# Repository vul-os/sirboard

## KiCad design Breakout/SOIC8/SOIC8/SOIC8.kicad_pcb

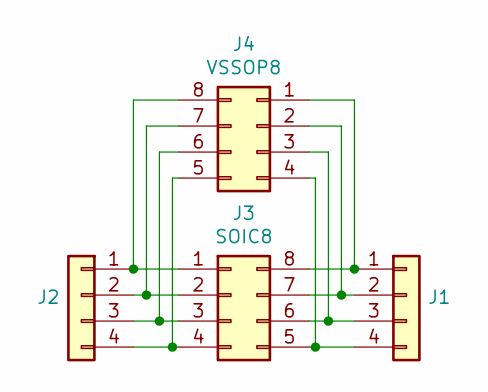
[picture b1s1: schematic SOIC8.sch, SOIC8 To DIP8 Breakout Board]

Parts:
J1, J2: Conn_01x04; PinHeader_1x04_P2.54mm_Vertical
J3: SOIC8; SOIC-8_3.9x4.9mm_P1.27mm
J4: VSSOP8; VSSOP-8_2.3x2mm_P0.5mm

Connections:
unnamed: J1.1, J3.8, J4.1
unnamed: J1.2, J3.7, J4.2
unnamed: J1.3, J3.6, J4.3
unnamed: J1.4, J3.5, J4.4
unnamed: J2.1, J3.1, J4.8
unnamed: J2.2, J3.2, J4.7
unnamed: J2.3, J3.3, J4.6
unnamed: J2.4, J3.4, J4.5

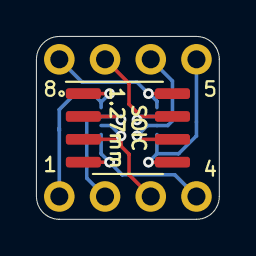
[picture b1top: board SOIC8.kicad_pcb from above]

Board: 2 copper layers, 10.2 x 10.2 mm, 4 parts (1 on the bottom side), 8 nets.

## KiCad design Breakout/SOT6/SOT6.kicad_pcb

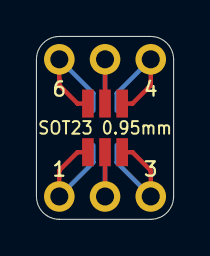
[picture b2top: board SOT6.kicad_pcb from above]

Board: 2 copper layers, 7.6 x 10.2 mm, 4 parts (1 on the bottom side), 6 nets.

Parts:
J1, J2: Conn_01x03; PinHeader_1x03_P2.54mm_Vertical
J3: Conn_02x03_Counter_Clockwise; SOT-23-6_Handsoldering
J4: Conn_02x03_Counter_Clockwise; SOT-363_SC-70-6_Handsoldering

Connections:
unnamed: J1.1, J3.6, J4.1
unnamed: J1.2, J3.5, J4.2
unnamed: J1.3, J3.4, J4.3
unnamed: J2.1, J3.1, J4.6
unnamed: J2.2, J3.2, J4.5
unnamed: J2.3, J3.3, J4.4

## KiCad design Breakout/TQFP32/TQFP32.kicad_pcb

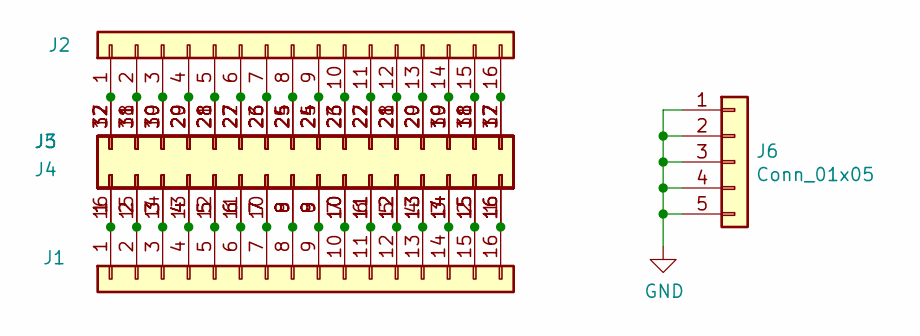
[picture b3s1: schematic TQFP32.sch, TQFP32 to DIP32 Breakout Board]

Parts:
J1, J2: Conn_01x16; PinHeader_1x16_P2.54mm_Vertical
J3: Conn_02x16_Counter_Clockwise; TQFP-32_7x7mm_P0.8mm
J4: Conn_02x16_Counter_Clockwise; LQFP-32_5x5mm_P0.5mm
J5: Conn_02x16_Counter_Clockwise; QFN-32-1EP_4x4mm_P0.4mm_EP2.65x2.65mm
J6: Conn_01x05; PinHeader_1x05_P2.54mm_Vertical

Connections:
GND: J5.33, J6.1, J6.2, J6.3, J6.4, J6.5
unnamed: J1.1, J3.1, J4.16, J5.1
unnamed: J1.2, J3.2, J4.15, J5.2
unnamed: J1.3, J3.3, J4.14, J5.3
unnamed: J1.4, J3.4, J4.13, J5.4
unnamed: J1.5, J3.5, J4.12, J5.5
unnamed: J1.6, J3.6, J4.11, J5.6
unnamed: J1.7, J3.7, J4.10, J5.7
unnamed: J1.8, J3.8, J4.9, J5.8
unnamed: J1.9, J3.9, J4.8, J5.9
unnamed: J1.10, J3.10, J4.7, J5.10
unnamed: J1.11, J3.11, J4.6, J5.11
unnamed: J1.12, J3.12, J4.5, J5.12
unnamed: J1.13, J3.13, J4.4, J5.13
unnamed: J1.14, J3.14, J4.3, J5.14
unnamed: J1.15, J3.15, J4.2, J5.15
unnamed: J1.16, J3.16, J4.1, J5.16
unnamed: J2.1, J3.32, J4.17, J5.32
unnamed: J2.2, J3.31, J4.18, J5.31
unnamed: J2.3, J3.30, J4.19, J5.30
unnamed: J2.4, J3.29, J4.20, J5.29
unnamed: J2.5, J3.28, J4.21, J5.28
unnamed: J2.6, J3.27, J4.22, J5.27
unnamed: J2.7, J3.26, J4.23, J5.26
unnamed: J2.8, J3.25, J4.24, J5.25
unnamed: J2.9, J3.24, J4.25, J5.24
unnamed: J2.10, J3.23, J4.26, J5.23
unnamed: J2.11, J3.22, J4.27, J5.22
unnamed: J2.12, J3.21, J4.28, J5.21
unnamed: J2.13, J3.20, J4.29, J5.20
unnamed: J2.14, J3.19, J4.30, J5.19
unnamed: J2.15, J3.18, J4.31, J5.18
unnamed: J2.16, J3.17, J4.32, J5.17

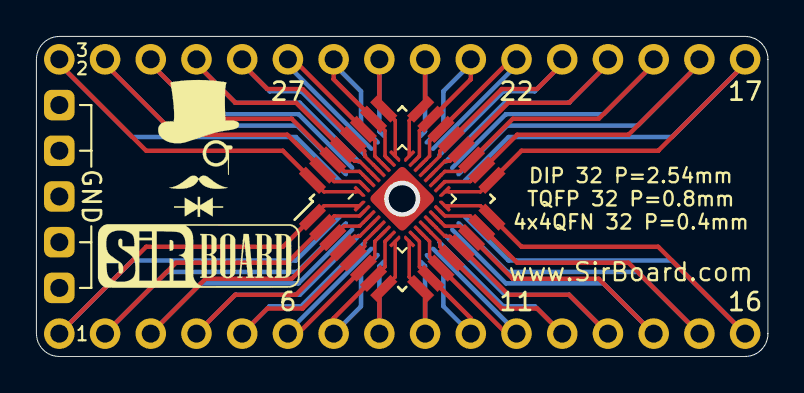
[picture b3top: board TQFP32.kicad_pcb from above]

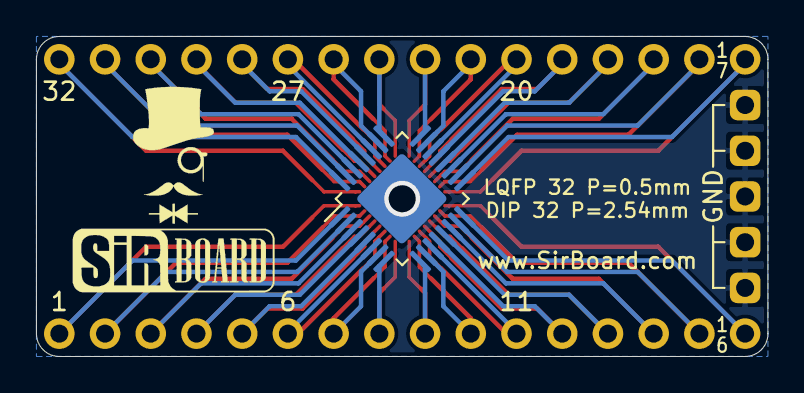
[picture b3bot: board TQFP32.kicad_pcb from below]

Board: 2 copper layers, 40.6 x 17.8 mm, 6 parts (3 on the bottom side), 33 nets.

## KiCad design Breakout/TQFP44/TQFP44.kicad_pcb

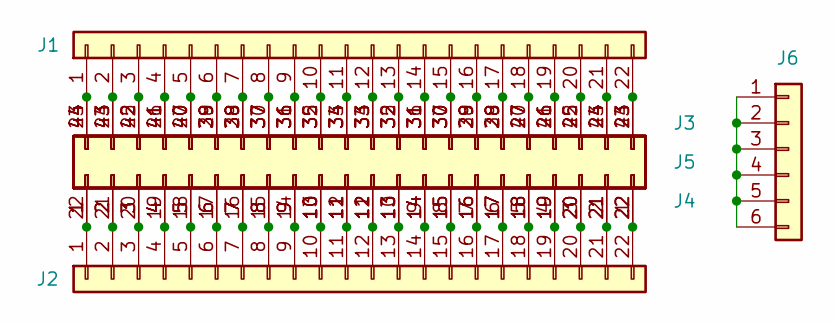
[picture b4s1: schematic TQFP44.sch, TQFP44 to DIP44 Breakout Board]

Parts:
J1, J2: Conn_01x22; PinHeader_1x22_P2.54mm_Vertical
J3, J5: Conn_02x22_Counter_Clockwise; TQFP-44_10x10mm_P0.8mm
J4: Conn_02x22_Counter_Clockwise; QFN-44-1EP_7x7mm_P0.5mm_EP5.15x5.15mm
J6: Conn_01x06; PinHeader_1x06_P2.54mm_Horizontal

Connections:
unnamed: J1.1, J3.44, J4.44, J5.23
unnamed: J1.2, J3.43, J4.43, J5.24
unnamed: J1.3, J3.42, J4.42, J5.25
unnamed: J1.4, J3.41, J4.41, J5.26
unnamed: J1.5, J3.40, J4.40, J5.27
unnamed: J1.6, J3.39, J4.39, J5.28
unnamed: J1.7, J3.38, J4.38, J5.29
unnamed: J1.8, J3.37, J4.37, J5.30
unnamed: J1.9, J3.36, J4.36, J5.31
unnamed: J1.10, J3.35, J4.35, J5.32
unnamed: J1.11, J3.34, J4.34, J5.33
unnamed: J1.12, J3.33, J4.33, J5.34
unnamed: J1.13, J3.32, J4.32, J5.35
unnamed: J1.14, J3.31, J4.31, J5.36
unnamed: J1.15, J3.30, J4.30, J5.37
unnamed: J1.16, J3.29, J4.29, J5.38
unnamed: J1.17, J3.28, J4.28, J5.39
unnamed: J1.18, J3.27, J4.27, J5.40
unnamed: J1.19, J3.26, J4.26, J5.41
unnamed: J1.20, J3.25, J4.25, J5.42
unnamed: J1.21, J3.24, J4.24, J5.43
unnamed: J1.22, J3.23, J4.23, J5.44
unnamed: J2.1, J3.1, J4.1, J5.22
unnamed: J2.2, J3.2, J4.2, J5.21
unnamed: J2.3, J3.3, J4.3, J5.20
unnamed: J2.4, J3.4, J4.4, J5.19
unnamed: J2.5, J3.5, J4.5, J5.18
unnamed: J2.6, J3.6, J4.6, J5.17
unnamed: J2.7, J3.7, J4.7, J5.16
unnamed: J2.8, J3.8, J4.8, J5.15
unnamed: J2.9, J3.9, J4.9, J5.14
unnamed: J2.10, J3.10, J4.10, J5.13
unnamed: J2.11, J3.11, J4.11, J5.12
unnamed: J2.12, J3.12, J4.12, J5.11
unnamed: J2.13, J3.13, J4.13, J5.10
unnamed: J2.14, J3.14, J4.14, J5.9
unnamed: J2.15, J3.15, J4.15, J5.8
unnamed: J2.16, J3.16, J4.16, J5.7
unnamed: J2.17, J3.17, J4.17, J5.6
unnamed: J2.18, J3.18, J4.18, J5.5
unnamed: J2.19, J3.19, J4.19, J5.4
unnamed: J2.20, J3.20, J4.20, J5.3
unnamed: J2.21, J3.21, J4.21, J5.2
unnamed: J2.22, J3.22, J4.22, J5.1
unnamed: J4.45, J6.1, J6.2, J6.3, J6.4, J6.5, J6.6

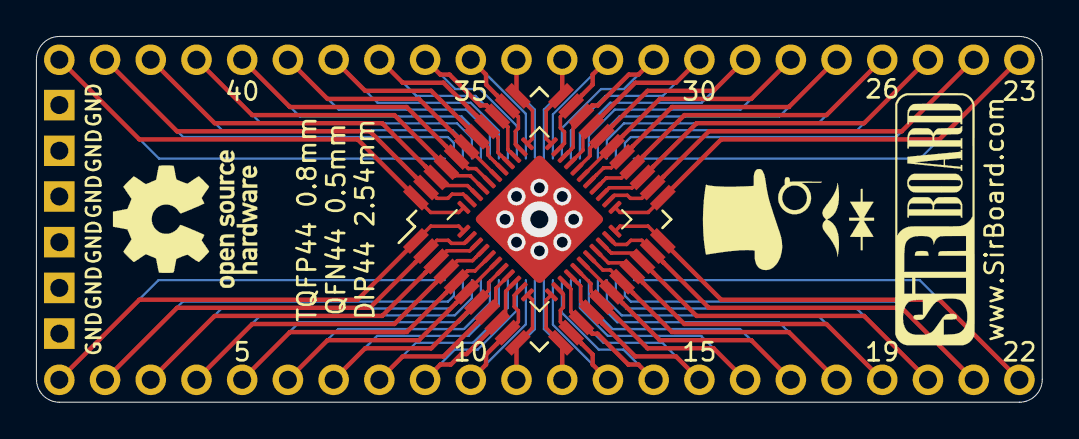
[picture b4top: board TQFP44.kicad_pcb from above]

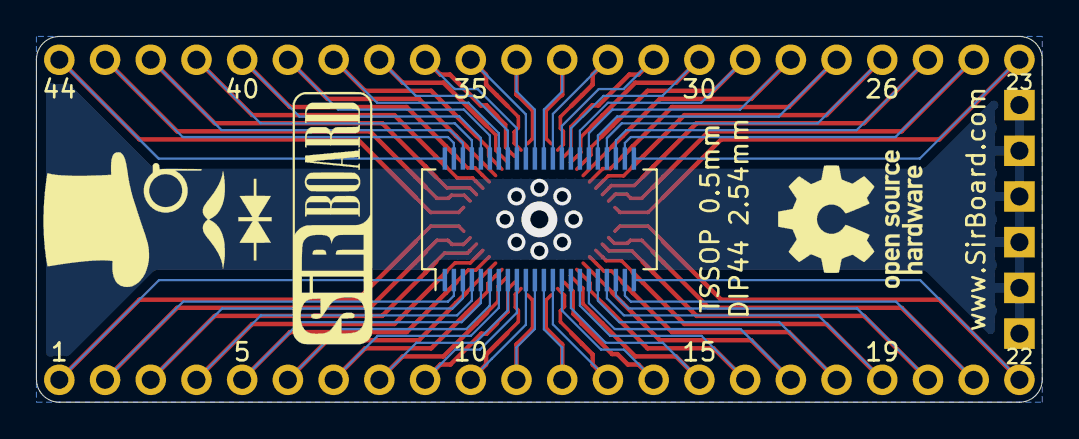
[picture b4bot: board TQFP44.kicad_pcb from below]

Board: 2 copper layers, 55.9 x 20.3 mm, 6 parts (2 on the bottom side), 45 nets.

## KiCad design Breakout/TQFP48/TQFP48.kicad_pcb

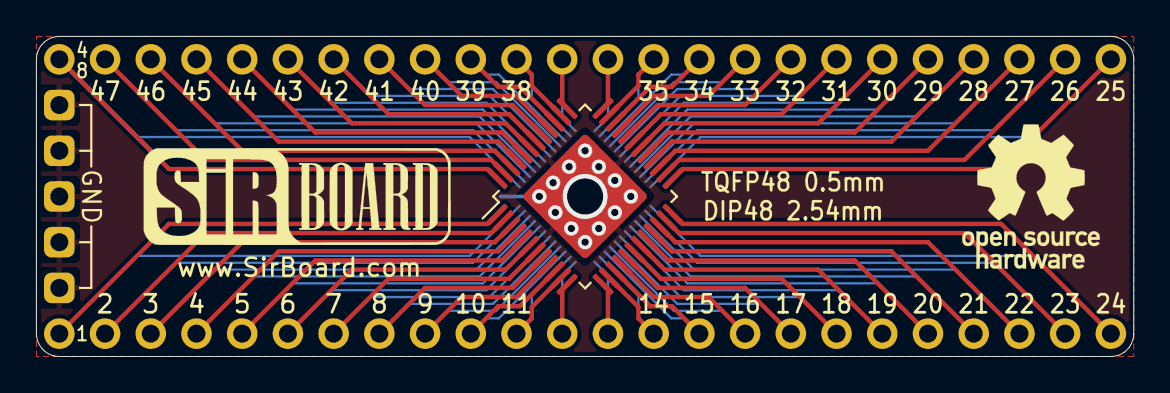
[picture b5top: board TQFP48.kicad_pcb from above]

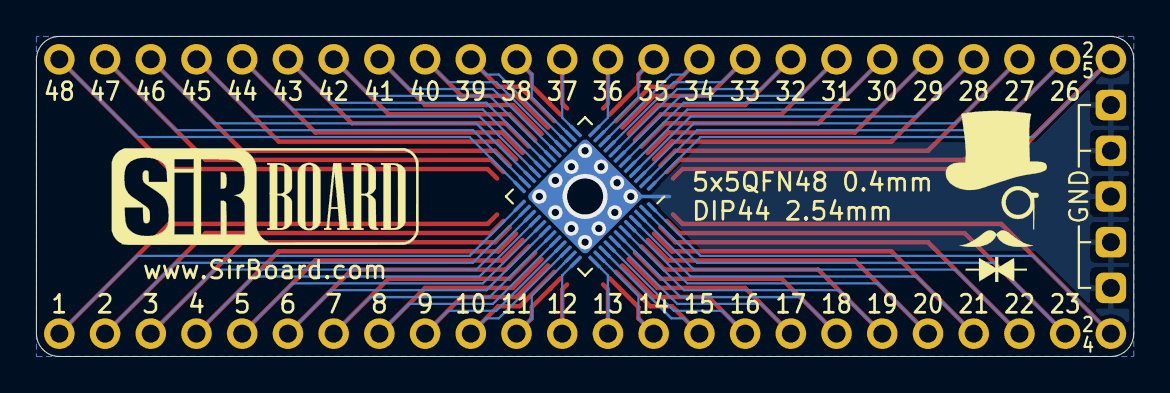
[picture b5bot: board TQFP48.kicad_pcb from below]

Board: 2 copper layers, 61.0 x 17.8 mm, 5 parts (4 on the bottom side), 49 nets.

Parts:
J1, J4: Conn_01x24; PinHeader_1x24_P2.54mm_Vertical
J2: Conn_02x24_Counter_Clockwise; TQFP-48-1EP_7x7mm_P0.5mm_EP5x5mm
J3: Conn_02x24_Counter_Clockwise; UQFN-48-1EP_6x6mm_P0.4mm_EP4.62x4.62mm
J5: Conn_01x05; PinHeader_1x05_P2.54mm_Vertical

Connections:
unnamed: J1.1, J2.1, J3.48
unnamed: J1.2, J2.2, J3.47
unnamed: J1.3, J2.3, J3.46
unnamed: J1.4, J2.4, J3.45
unnamed: J1.5, J2.5, J3.44
unnamed: J1.6, J2.6, J3.43
unnamed: J1.7, J2.7, J3.42
unnamed: J1.8, J2.8, J3.41
unnamed: J1.9, J2.9, J3.40
unnamed: J1.10, J2.10, J3.39
unnamed: J1.11, J2.11, J3.38
unnamed: J1.12, J2.12, J3.37
unnamed: J1.13, J2.13, J3.36
unnamed: J1.14, J2.14, J3.35
unnamed: J1.15, J2.15, J3.34
unnamed: J1.16, J2.16, J3.33
unnamed: J1.17, J2.17, J3.32
unnamed: J1.18, J2.18, J3.31
unnamed: J1.19, J2.19, J3.30
unnamed: J1.20, J2.20, J3.29
unnamed: J1.21, J2.21, J3.28
unnamed: J1.22, J2.22, J3.27
unnamed: J1.23, J2.23, J3.26
unnamed: J1.24, J2.24, J3.25
unnamed: J2.25, J3.24, J4.24
unnamed: J2.26, J3.23, J4.23
unnamed: J2.27, J3.22, J4.22
unnamed: J2.28, J3.21, J4.21
unnamed: J2.29, J3.20, J4.20
unnamed: J2.30, J3.19, J4.19
unnamed: J2.31, J3.18, J4.18
unnamed: J2.32, J3.17, J4.17
unnamed: J2.33, J3.16, J4.16
unnamed: J2.34, J3.15, J4.15
unnamed: J2.35, J3.14, J4.14
unnamed: J2.36, J3.13, J4.13
unnamed: J2.37, J3.12, J4.12
unnamed: J2.38, J3.11, J4.11
unnamed: J2.39, J3.10, J4.10
unnamed: J2.40, J3.9, J4.9
unnamed: J2.41, J3.8, J4.8
unnamed: J2.42, J3.7, J4.7
unnamed: J2.43, J3.6, J4.6
unnamed: J2.44, J3.5, J4.5
unnamed: J2.45, J3.4, J4.4
unnamed: J2.46, J3.3, J4.3
unnamed: J2.47, J3.2, J4.2
unnamed: J2.48, J3.1, J4.1
unnamed: J2.49, J3.49, J5.1, J5.2, J5.3, J5.4, J5.5

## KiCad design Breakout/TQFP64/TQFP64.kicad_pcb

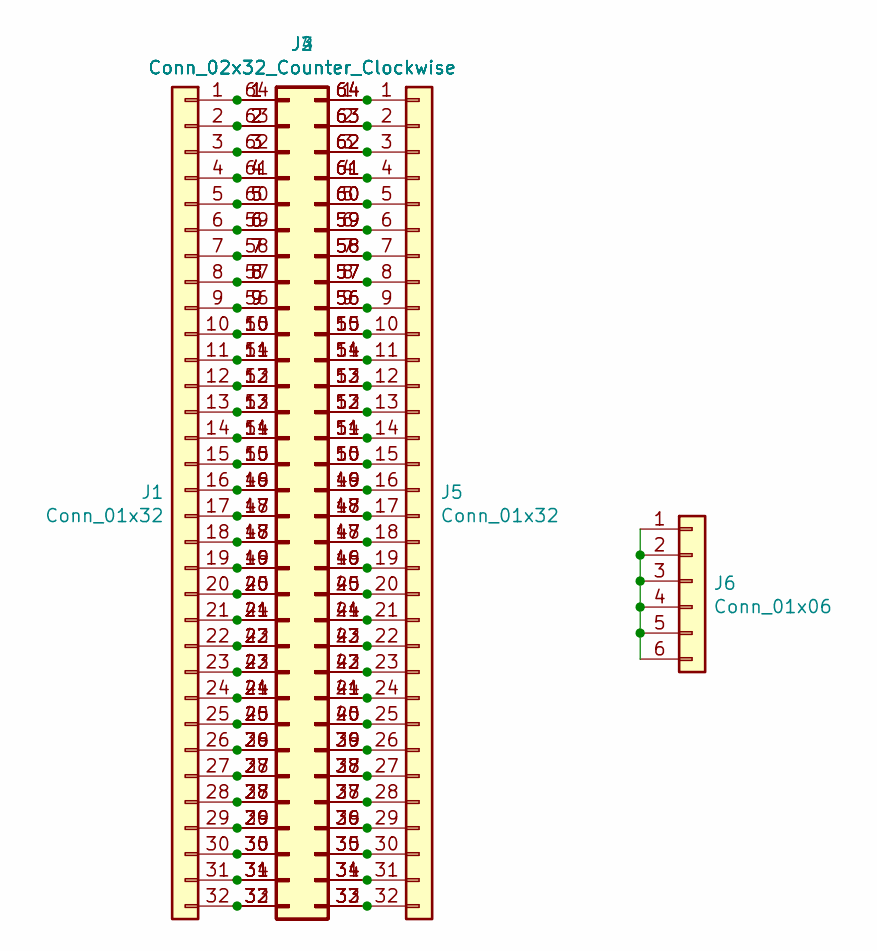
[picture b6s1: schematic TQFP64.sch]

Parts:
J1, J5: Conn_01x32; PinHeader_1x32_P2.54mm_Vertical
J2: Conn_02x32_Counter_Clockwise; TQFP-64_10x10mm_P0.5mm
J3: Conn_02x32_Counter_Clockwise; QFN-64-1EP_8x8mm_P0.4mm_EP6.5x6.5mm
J4: Conn_02x32_Counter_Clockwise; TQFP-64_7x7mm_P0.4mm
J6: Conn_01x06; PinHeader_1x06_P2.54mm_Vertical

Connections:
unnamed: J1.1, J2.1, J3.1, J4.64
unnamed: J1.2, J2.2, J3.2, J4.63
unnamed: J1.3, J2.3, J3.3, J4.62
unnamed: J1.4, J2.4, J3.4, J4.61
unnamed: J1.5, J2.5, J3.5, J4.60
unnamed: J1.6, J2.6, J3.6, J4.59
unnamed: J1.7, J2.7, J3.7, J4.58
unnamed: J1.8, J2.8, J3.8, J4.57
unnamed: J1.9, J2.9, J3.9, J4.56
unnamed: J1.10, J2.10, J3.10, J4.55
unnamed: J1.11, J2.11, J3.11, J4.54
unnamed: J1.12, J2.12, J3.12, J4.53
unnamed: J1.13, J2.13, J3.13, J4.52
unnamed: J1.14, J2.14, J3.14, J4.51
unnamed: J1.15, J2.15, J3.15, J4.50
unnamed: J1.16, J2.16, J3.16, J4.49
unnamed: J1.17, J2.17, J3.17, J4.48
unnamed: J1.18, J2.18, J3.18, J4.47
unnamed: J1.19, J2.19, J3.19, J4.46
unnamed: J1.20, J2.20, J3.20, J4.45
unnamed: J1.21, J2.21, J3.21, J4.44
unnamed: J1.22, J2.22, J3.22, J4.43
unnamed: J1.23, J2.23, J3.23, J4.42
unnamed: J1.24, J2.24, J3.24, J4.41
unnamed: J1.25, J2.25, J3.25, J4.40
unnamed: J1.26, J2.26, J3.26, J4.39
unnamed: J1.27, J2.27, J3.27, J4.38
unnamed: J1.28, J2.28, J3.28, J4.37
unnamed: J1.29, J2.29, J3.29, J4.36
unnamed: J1.30, J2.30, J3.30, J4.35
unnamed: J1.31, J2.31, J3.31, J4.34
unnamed: J1.32, J2.32, J3.32, J4.33
unnamed: J2.33, J3.33, J4.32, J5.32
unnamed: J2.34, J3.34, J4.31, J5.31
unnamed: J2.35, J3.35, J4.30, J5.30
unnamed: J2.36, J3.36, J4.29, J5.29
unnamed: J2.37, J3.37, J4.28, J5.28
unnamed: J2.38, J3.38, J4.27, J5.27
unnamed: J2.39, J3.39, J4.26, J5.26
unnamed: J2.40, J3.40, J4.25, J5.25
unnamed: J2.41, J3.41, J4.24, J5.24
unnamed: J2.42, J3.42, J4.23, J5.23
unnamed: J2.43, J3.43, J4.22, J5.22
unnamed: J2.44, J3.44, J4.21, J5.21
unnamed: J2.45, J3.45, J4.20, J5.20
unnamed: J2.46, J3.46, J4.19, J5.19
unnamed: J2.47, J3.47, J4.18, J5.18
unnamed: J2.48, J3.48, J4.17, J5.17
unnamed: J2.49, J3.49, J4.16, J5.16
unnamed: J2.50, J3.50, J4.15, J5.15
unnamed: J2.51, J3.51, J4.14, J5.14
unnamed: J2.52, J3.52, J4.13, J5.13
unnamed: J2.53, J3.53, J4.12, J5.12
unnamed: J2.54, J3.54, J4.11, J5.11
unnamed: J2.55, J3.55, J4.10, J5.10
unnamed: J2.56, J3.56, J4.9, J5.9
unnamed: J2.57, J3.57, J4.8, J5.8
unnamed: J2.58, J3.58, J4.7, J5.7
unnamed: J2.59, J3.59, J4.6, J5.6
unnamed: J2.60, J3.60, J4.5, J5.5
unnamed: J2.61, J3.61, J4.4, J5.4
unnamed: J2.62, J3.62, J4.3, J5.3
unnamed: J2.63, J3.63, J4.2, J5.2
unnamed: J2.64, J3.64, J4.1, J5.1
unnamed: J3.65, J6.1, J6.2, J6.3, J6.4, J6.5, J6.6

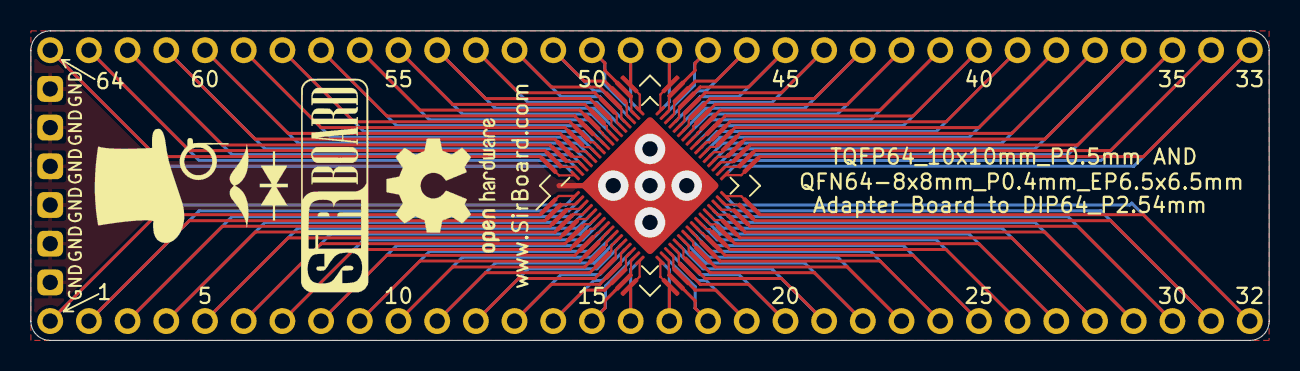
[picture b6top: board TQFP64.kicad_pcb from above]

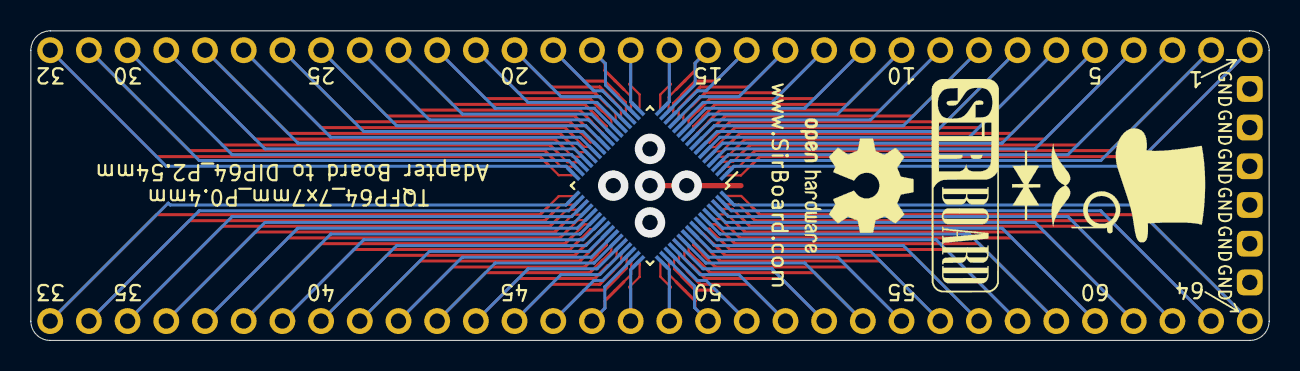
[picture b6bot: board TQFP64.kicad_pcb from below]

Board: 2 copper layers, 81.3 x 20.3 mm, 6 parts (4 on the bottom side), 65 nets.

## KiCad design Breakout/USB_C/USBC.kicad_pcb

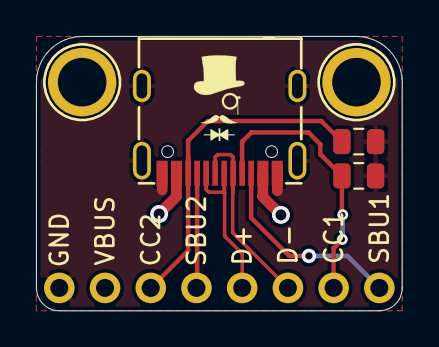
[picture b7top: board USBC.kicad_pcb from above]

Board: 2 copper layers, 20.3 x 15.2 mm, 6 parts (0 on the bottom side), 8 nets.

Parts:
H1, H2: MountingHole; MountingHole_M2.5_SirBoard
J1: USB_C_Receptacle_USB2.0; USB_C
J2: Conn_01x08; PinHeader_1x08_P2.54mm_Vertical
R1, R2: 5K1; R_0805_2012Metric

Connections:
/CC1: J1.A5, J2.7, R1.2
/CC2: J1.B5, J2.3, R2.2
/D+: J1.A6, J1.B6, J2.5
/D-: J1.A7, J1.B7, J2.6
/SBU1: J1.A8, J2.4
/SBU2: J1.B8, J2.8
/VBUS: J1.A4, J1.A9, J1.B4, J1.B9, J2.2
GND: J1.A1, J1.A12, J1.B1, J1.B12, J1.S1, J2.1, R1.1, R2.1

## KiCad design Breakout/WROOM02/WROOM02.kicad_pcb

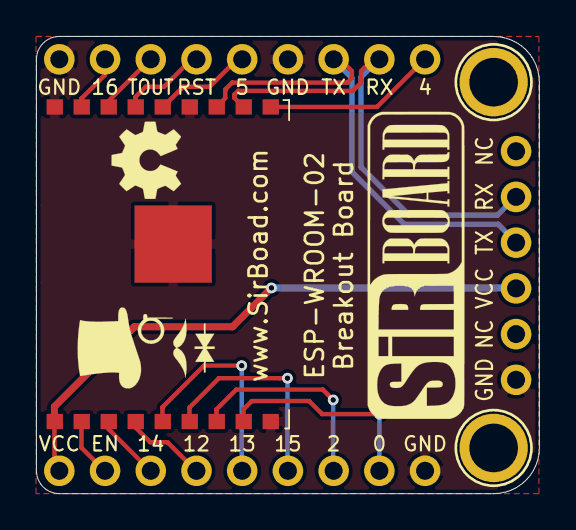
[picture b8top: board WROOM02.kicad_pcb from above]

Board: 2 copper layers, 27.9 x 25.4 mm, 6 parts (0 on the bottom side), 16 nets.

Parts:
H1, H2: MountingHole; MountingHole_M2.5_SirBoard
J1, J2: Conn_01x09; PinHeader_1x09_P2.54mm_Vertical
J3: Conn_01x06; PinHeader_1x06_P2.54mm_Vertical
U1: ESP-WROOM-02

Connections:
EN: J1.2, U1.2
GND: J1.9, J2.1, J2.6, J3.1, U1.9, U1.13, U1.18, U1.19
GPI16: J2.2, U1.17
GPIO0: J1.8, U1.8
GPIO2: J1.7, U1.7
GPIO4: J2.9, U1.10
GPIO5: J2.5, U1.14
GPIO12: J1.4, U1.4
GPIO13: J1.5, U1.5
GPIO14: J1.3, U1.3
GPIO15: J1.6, U1.6
RST: J2.4, U1.15
RXD: J2.8, J3.5, U1.11
TOUT: J2.3, U1.16
TXD: J2.7, J3.4, U1.12
VCC: J1.1, J3.3, U1.1
